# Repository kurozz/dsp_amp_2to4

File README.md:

DSP Amplifier - 2 inputs 4 outputs
Amplifier with DSP based on TPA3116D2 and ADAU1701 with 4 outputs and stereo input.

DSP programming can be done with SigmaStudio and needs an appropriate programmer.
How to program: https://daumemo.com/how-to-program-an-analog-devices-dsp/

Hackaday.io: https://hackaday.io/project/182993-dsp-amplifier-2-inputs-4-outputs
Project at PCBWAY (I get some credits if you buy the PCB from this link): https://www.pcbway.com/project/shareproject/DSP_Amplifier___2_inputs_4_outputs.html

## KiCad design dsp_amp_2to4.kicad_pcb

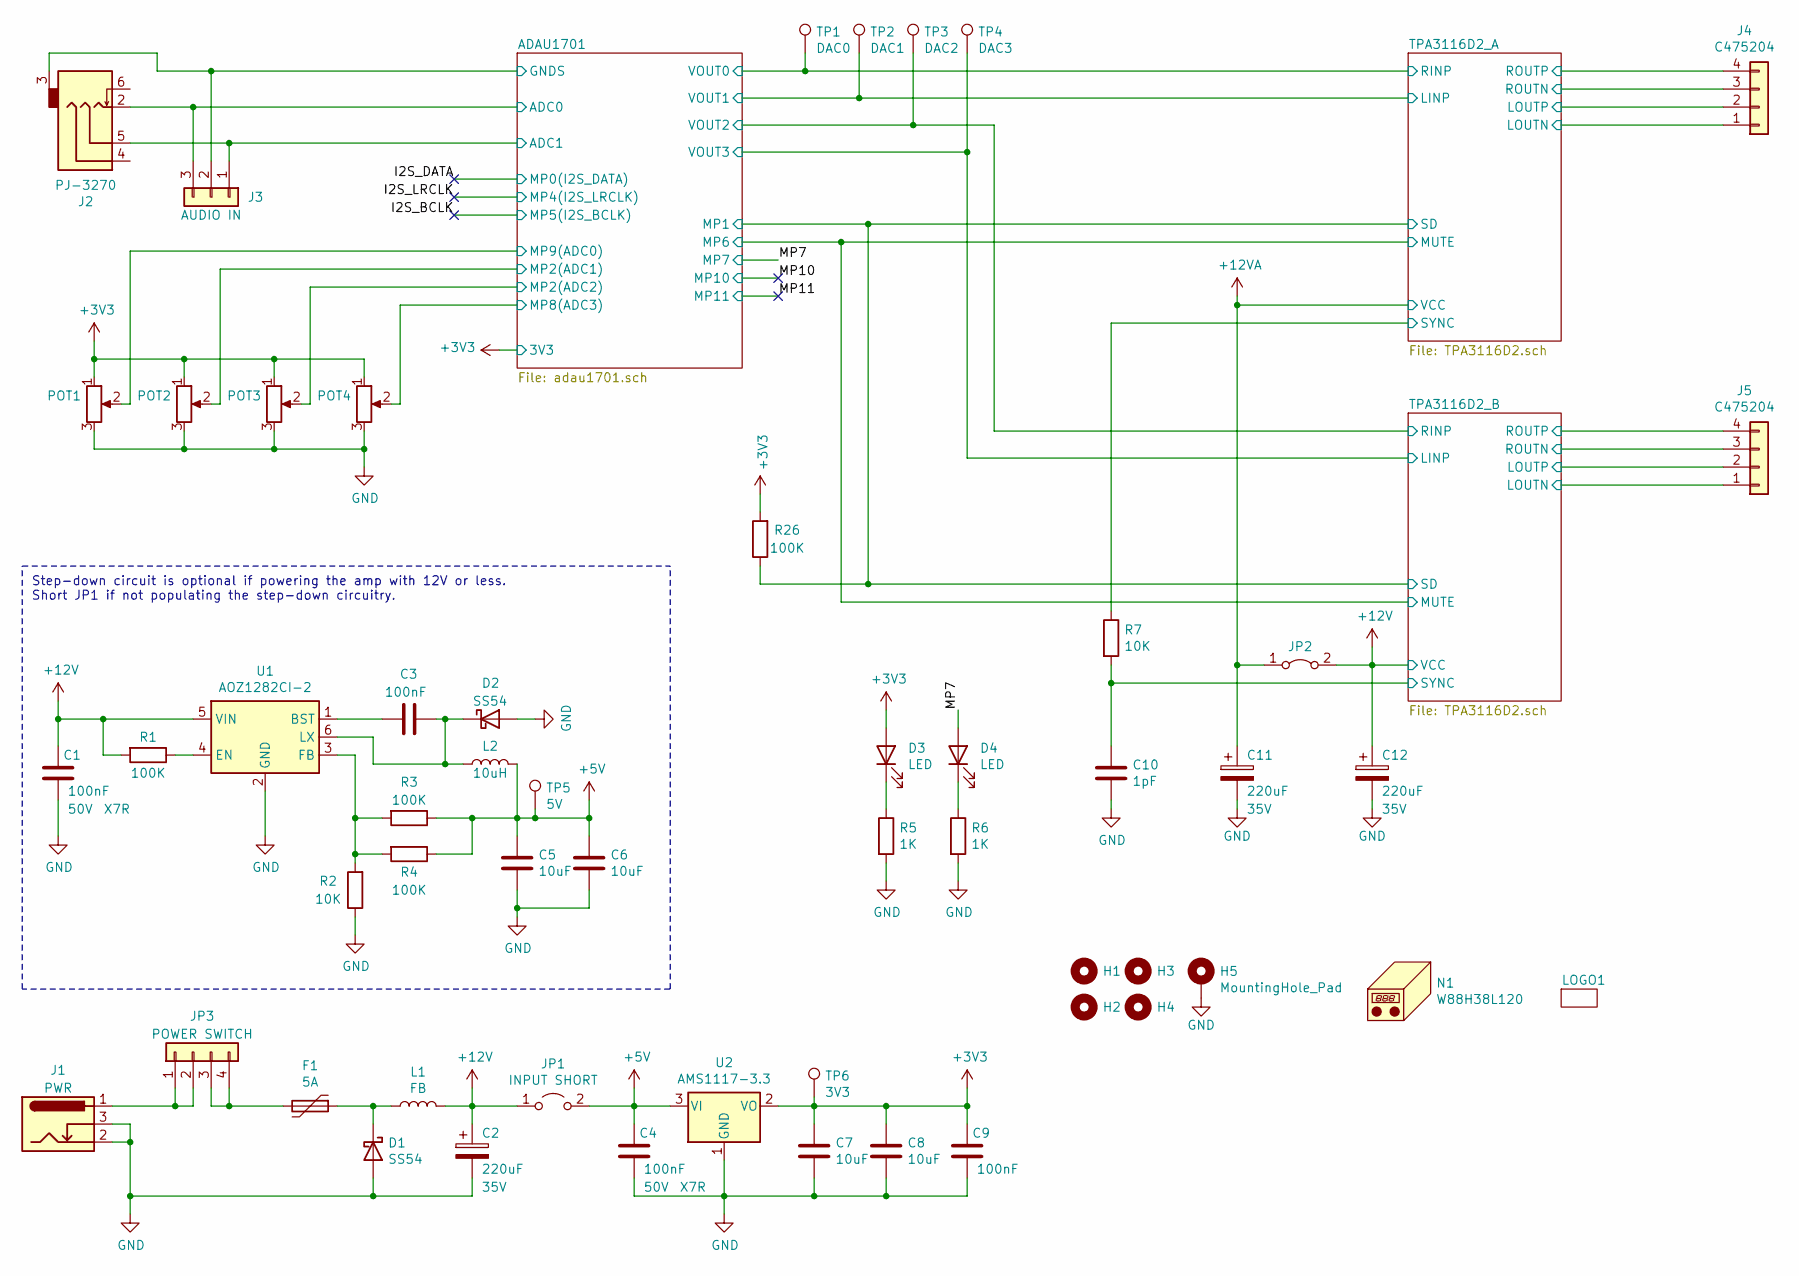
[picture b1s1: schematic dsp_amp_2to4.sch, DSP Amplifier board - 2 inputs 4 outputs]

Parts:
C1, C3, C4, C9: 100nF; C_0603_1608Metric; Rating X7R; Voltage 50V; LCSC Part Number C14663
C2, C11, C12: 220uF; CP_Radial_D8.0mm_P3.50mm; Voltage 35V; LCSC Part Number C433284
C5, C6, C7, C8: 10uF; C_0603_1608Metric; LCSC Part Number C85713
C10: 1pF; C_0603_1608Metric
D1, D2: SS54; D_SMA; LCSC Part Number C908681
D3, D4: LED; LED_D3.0mm; LCSC Part Number C710207
F1: 5A; Fuse_1206_3216Metric; LCSC Part Number C99541
H1, H2, H3, H4: MountingHole; MountingHole_3.2mm_M3
H5: MountingHole_Pad; MountingHole_3.2mm_M3_Pad_Via
J1: PWR; C381116; LCSC Part Number C381116
J2: PJ-3270; LCSC Part Number C381134
J3: JST XH-B3B; JST_XH_B3B-XH-A_1x03_P2.50mm_Vertical; LCSC Part Number C2316
J4, J5: C475204; LCSC Part Number C475204
JP1: INPUT SHORT; SolderJumper-2_P1.3mm_Open_TrianglePad1.0x1.5mm
JP2: Jumper Wire; R_Axial_DIN0204_L3.6mm_D1.6mm_P7.62mm_Horizontal
JP3: POWER SWITCH; JST_XH_B4B-XH-A_1x04_P2.50mm_Vertical
L1: FB; L_0805_2012Metric; LCSC Part Number C304323
L2: 10uH; L_6.3x6.3_H3; LCSC Part Number C207842
LOGO1: logo; shamiko
N1: W88H38L120; Aluminum_W88H38L120
POT1, POT2, POT3, POT4: JST XH-B3B; JST_XH_B3B-XH-A_1x03_P2.50mm_Vertical; LCSC Part Number C2316
R1, R3, R4, R26: 100K; R_0603_1608Metric; LCSC Part Number C14675
R2, R7: 10K; R_0603_1608Metric; LCSC Part Number C98220
R5, R6: 1K; R_0603_1608Metric; LCSC Part Number C22548
TP1: DAC0; TestPoint_THTPad_D1.0mm_Drill0.5mm
TP2: DAC1; TestPoint_THTPad_D1.0mm_Drill0.5mm
TP3: DAC2; TestPoint_THTPad_D1.0mm_Drill0.5mm
TP4: DAC3; TestPoint_THTPad_D1.0mm_Drill0.5mm
TP5: 5V; TestPoint_THTPad_D1.0mm_Drill0.5mm
TP6: 3V3; TestPoint_THTPad_D1.0mm_Drill0.5mm
U1: AOZ1282CI-2; SOT-23-6; LCSC Part Number C176766
U2: AMS1117-3.3; SOT-223-3_TabPin2; LCSC Part Number C347222

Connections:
+3V3: C7.1, C8.1, C9.1, D3.2 (A), POT1.1, POT2.1, POT3.1, POT4.1, R26.2, TP6.1, U2.2 (VO); also elsewhere on the board
+5V: C4.1, C5.1, C6.1, JP1.2 (B), L2.2, R3.1, R4.1, TP5.1, U2.3 (VI)
+12V: C1.1, C2.1, C12.1, JP1.1 (A), JP2.2 (B), L1.2, R1.2, U1.5 (VIN); also elsewhere on the board
+12VA: C11.1, JP2.1 (A); also elsewhere on the board
/ADAU1701/ADC0: J2.2, J3.3; also elsewhere on the board
/ADAU1701/ADC1: J2.5, J3.1; also elsewhere on the board
/ADAU1701/GNDS: J2.3, J3.2; also elsewhere on the board
/ADAU1701/MP1: R26.1; also elsewhere on the board
/ADAU1701/MP2(ADC1): POT2.2; also elsewhere on the board
/ADAU1701/MP2(ADC2): POT3.2; also elsewhere on the board
/ADAU1701/MP8(ADC3): POT4.2; also elsewhere on the board
/ADAU1701/MP9(ADC0): POT1.2; also elsewhere on the board
/MP7: D4.2 (A); also elsewhere on the board
/TPA3116D2_A/LINP: TP2.1; also elsewhere on the board
/TPA3116D2_A/LOUTN: J4.1; also elsewhere on the board
/TPA3116D2_A/LOUTP: J4.2; also elsewhere on the board
/TPA3116D2_A/RINP: TP1.1; also elsewhere on the board
/TPA3116D2_A/ROUTN: J4.3; also elsewhere on the board
/TPA3116D2_A/ROUTP: J4.4; also elsewhere on the board
/TPA3116D2_A/SYNC: R7.1; also elsewhere on the board
/TPA3116D2_B/LINP: TP4.1; also elsewhere on the board
/TPA3116D2_B/LOUTN: J5.1; also elsewhere on the board
/TPA3116D2_B/LOUTP: J5.2; also elsewhere on the board
/TPA3116D2_B/RINP: TP3.1; also elsewhere on the board
/TPA3116D2_B/ROUTN: J5.3; also elsewhere on the board
/TPA3116D2_B/ROUTP: J5.4; also elsewhere on the board
/TPA3116D2_B/SYNC: C10.1, R7.2; also elsewhere on the board
GND: C1.2, C2.2, C4.2, C5.2, C6.2, C7.2, C8.2, C9.2, C10.2, C11.2, C12.2, D1.2 (A), D2.2 (A), H5.1, J1.2, J1.3, POT1.3, POT2.3, POT3.3, POT4.3, R2.1, R5.2, R6.2, U1.2 (GND), U2.1 (GND); also elsewhere on the board
unnamed: C3.1, U1.1 (BST)
unnamed: C3.2, D2.1 (K), L2.1, U1.6 (LX)
unnamed: D1.1 (K), F1.1, L1.1
unnamed: D3.1 (K), R5.1
unnamed: D4.1 (K), R6.1
unnamed: F1.2, JP3.3, JP3.4
unnamed: J1.1, JP3.1, JP3.2
unnamed: R1.1, U1.4 (EN)
unnamed: R2.2, R3.2, R4.2, U1.3 (FB)

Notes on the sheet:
Step-down circuit is optional if powering the amp with 12V or less. Short JP1 if not populating the step-down circuitry.

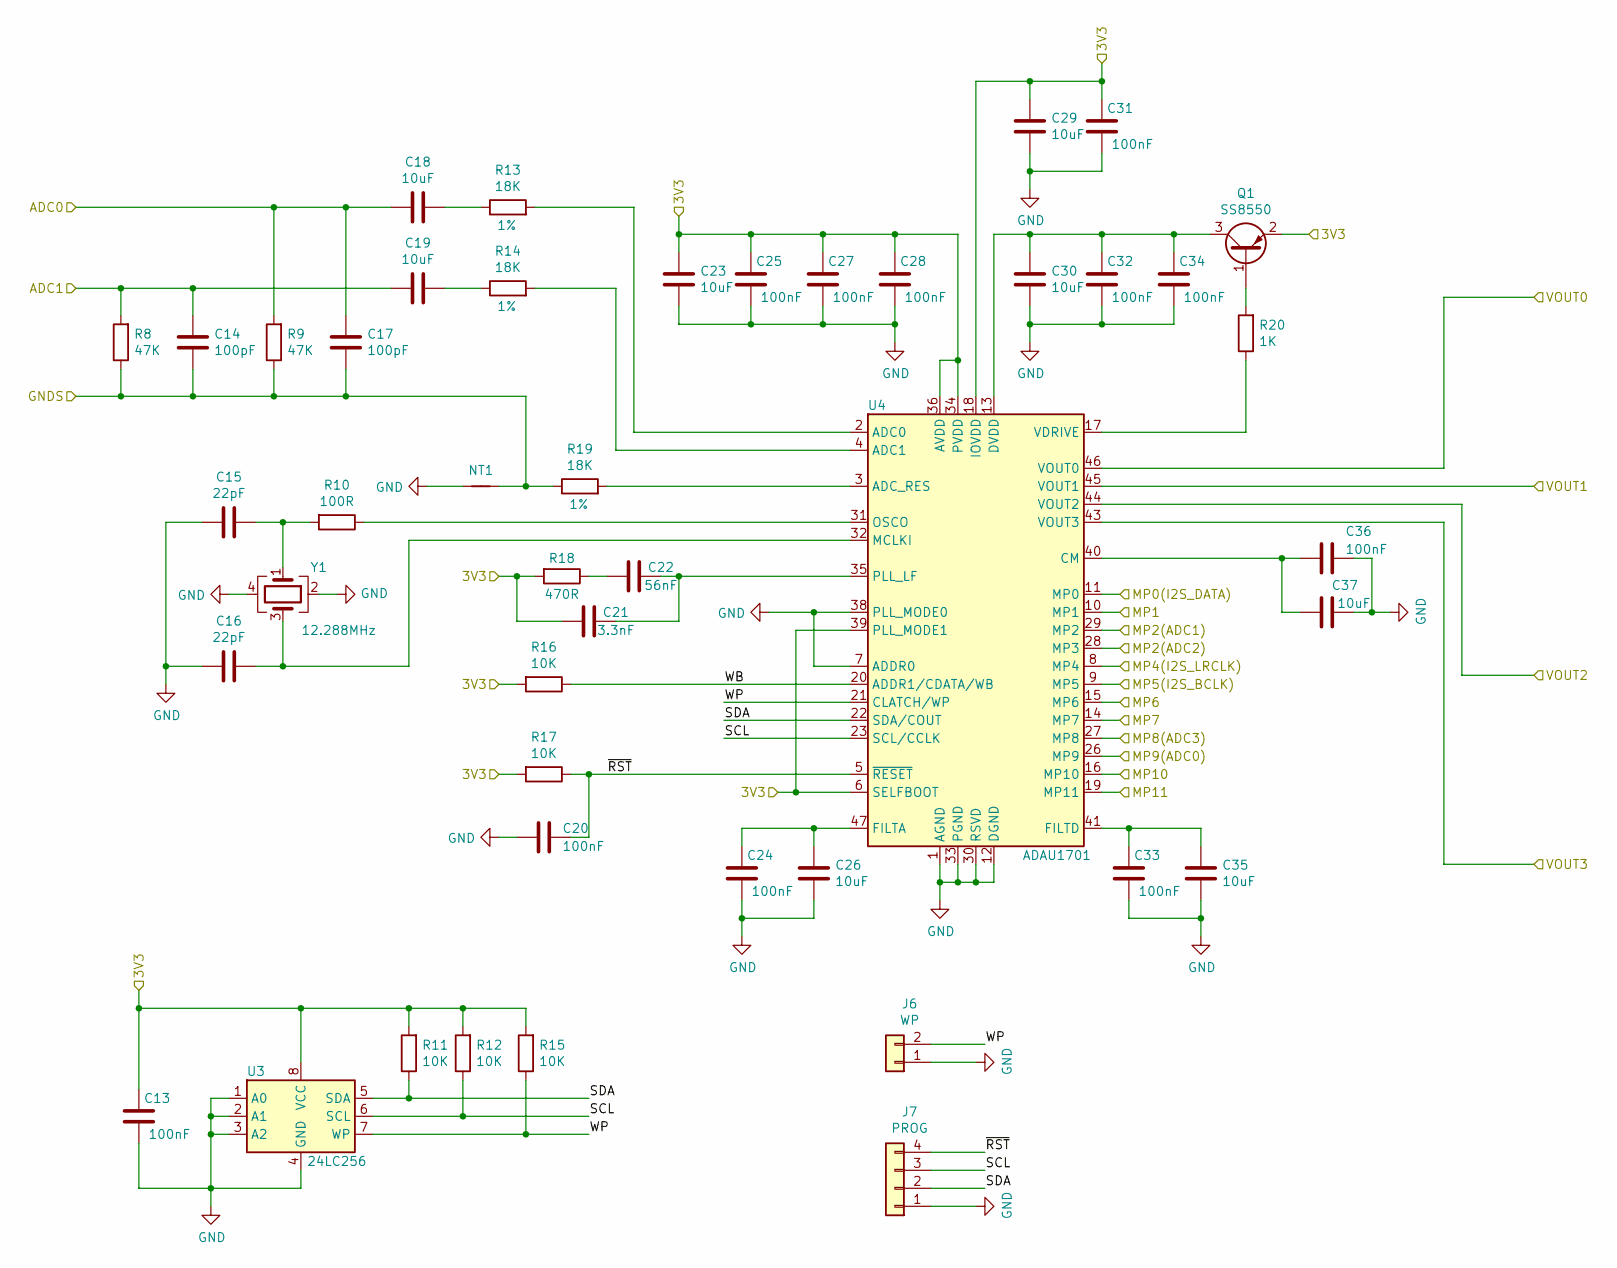
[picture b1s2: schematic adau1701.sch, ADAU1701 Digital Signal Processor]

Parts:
C13, C20, C24, C25, C27, C28, C31, C32, C33, C34, C36: 100nF; C_0603_1608Metric; Rating X7R; Voltage 50V; LCSC Part Number C14663
C14, C17: 100pF; C_0603_1608Metric; LCSC Part Number C14665
C15, C16: 22pF; C_0603_1608Metric; LCSC Part Number C105620
C18, C19, C23, C26, C29, C30, C35, C37: 10uF; C_0603_1608Metric; LCSC Part Number C85713
C21: 3.3nF; C_0603_1608Metric; LCSC Part Number C107088
C22: 56nF; C_0603_1608Metric; LCSC Part Number C282072
J6: WP; PinHeader_1x02_P2.54mm_Vertical
J7: PROG; PinHeader_1x04_P2.54mm_Vertical
NT1: Net-Tie_2; NetTie-2_SMD_Pad0.5mm
Q1: SS8550; SOT-23; LCSC Part Number C545534
R8, R9: 47K; R_0603_1608Metric; LCSC Part Number C105579
R10: 100R; R_0603_1608Metric; LCSC Part Number C105588
R11, R12, R15, R16, R17: 10K; R_0603_1608Metric; LCSC Part Number C98220
R13, R14, R19: 18K; R_0603_1608Metric; Tolerance 1%; LCSC Part Number C114610
R18: 470R; R_0603_1608Metric; LCSC Part Number C114669
R20: 1K; R_0603_1608Metric; LCSC Part Number C22548
U3: 24LC256; SOIC-8_3.9x4.9mm_P1.27mm; LCSC Part Number C5458
U4: ADAU1701; LQFP-48_7x7mm_P0.5mm; LCSC Part Number C389590
Y1: 12.288MHz; Crystal_SMD_SeikoEpson_FA238-4Pin_3.2x2.5mm; LCSC Part Number C389826

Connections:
+3V3: C13.1, C21.2, C23.1, C25.1, C27.1, C28.1, C29.1, C31.1, Q1.2 (E), R11.2, R12.2, R15.2, R16.2, R17.2, R18.2, U3.8 (VCC), U4.6 (SELFBOOT), U4.18 (IOVDD), U4.34 (PVDD), U4.36 (AVDD), U4.39 (PLL_MODE1), U4.48 (AVDD); also elsewhere on the board
/ADAU1701/ADC0: C17.2, C18.1, R9.2; also elsewhere on the board
/ADAU1701/ADC1: C14.2, C19.1, R8.2; also elsewhere on the board
/ADAU1701/GNDS: C14.1, C17.1, NT1.2, R8.1, R9.1, R19.1; also elsewhere on the board
/ADAU1701/MP1: U4.10 (MP1); also elsewhere on the board
/ADAU1701/MP2(ADC1): U4.29 (MP2); also elsewhere on the board
/ADAU1701/MP2(ADC2): U4.28 (MP3); also elsewhere on the board
/ADAU1701/MP6: U4.15 (MP6); also elsewhere on the board
/ADAU1701/MP8(ADC3): U4.27 (MP8); also elsewhere on the board
/ADAU1701/MP9(ADC0): U4.26 (MP9); also elsewhere on the board
/ADAU1701/SCL: J7.3, R12.1, U3.6 (SCL), U4.23 (SCL/CCLK)
/ADAU1701/SDA: J7.2, R11.1, U3.5 (SDA), U4.22 (SDA/COUT)
/ADAU1701/WB: R16.1, U4.20 (ADDR1/CDATA/WB)
/ADAU1701/WP: J6.2, R15.1, U3.7 (WP), U4.21 (CLATCH/WP)
/ADAU1701/~RST: C20.1, J7.4, R17.1, U4.5 (~RESET)
/I2S_BCLK: U4.9 (MP5)
/I2S_DATA: U4.11 (MP0)
/I2S_LRCLK: U4.8 (MP4)
/MP7: U4.14 (MP7); also elsewhere on the board
/MP10: U4.16 (MP10)
/MP11: U4.19 (MP11)
/TPA3116D2_A/LINP: U4.45 (VOUT1); also elsewhere on the board
/TPA3116D2_A/RINP: U4.46 (VOUT0); also elsewhere on the board
/TPA3116D2_B/LINP: U4.43 (VOUT3); also elsewhere on the board
/TPA3116D2_B/RINP: U4.44 (VOUT2); also elsewhere on the board
GND: C13.2, C15.1, C16.1, C20.2, C23.2, C24.2, C25.2, C26.2, C27.2, C28.2, C29.2, C30.2, C31.2, C32.2, C33.2, C34.2, C35.2, C36.1, C37.1, J6.1, J7.1, NT1.1, U3.1 (A0), U3.2 (A1), U3.3 (A2), U3.4 (GND), U4.1 (AGND), U4.7 (ADDR0), U4.12 (DGND), U4.25 (DGND), U4.30 (RSVD), U4.33 (PGND), U4.37 (AGND), U4.38 (PLL_MODE0), U4.42 (AGND), Y1.2, Y1.4; also elsewhere on the board
unnamed: C15.2, R10.2, Y1.1
unnamed: C16.2, U4.32 (MCLKI), Y1.3
unnamed: C18.2, R13.1
unnamed: C19.2, R14.1
unnamed: C21.1, C22.1, U4.35 (PLL_LF)
unnamed: C22.2, R18.1
unnamed: C24.1, C26.1, U4.47 (FILTA)
unnamed: C30.1, C32.1, C34.1, Q1.3 (C), U4.13 (DVDD), U4.24 (DVDD)
unnamed: C33.1, C35.1, U4.41 (FILTD)
unnamed: C36.2, C37.2, U4.40 (CM)
unnamed: Q1.1 (B), R20.2
unnamed: R10.1, U4.31 (OSCO)
unnamed: R13.2, U4.2 (ADC0)
unnamed: R14.2, U4.4 (ADC1)
unnamed: R19.2, U4.3 (ADC_RES)
unnamed: R20.1, U4.17 (VDRIVE)

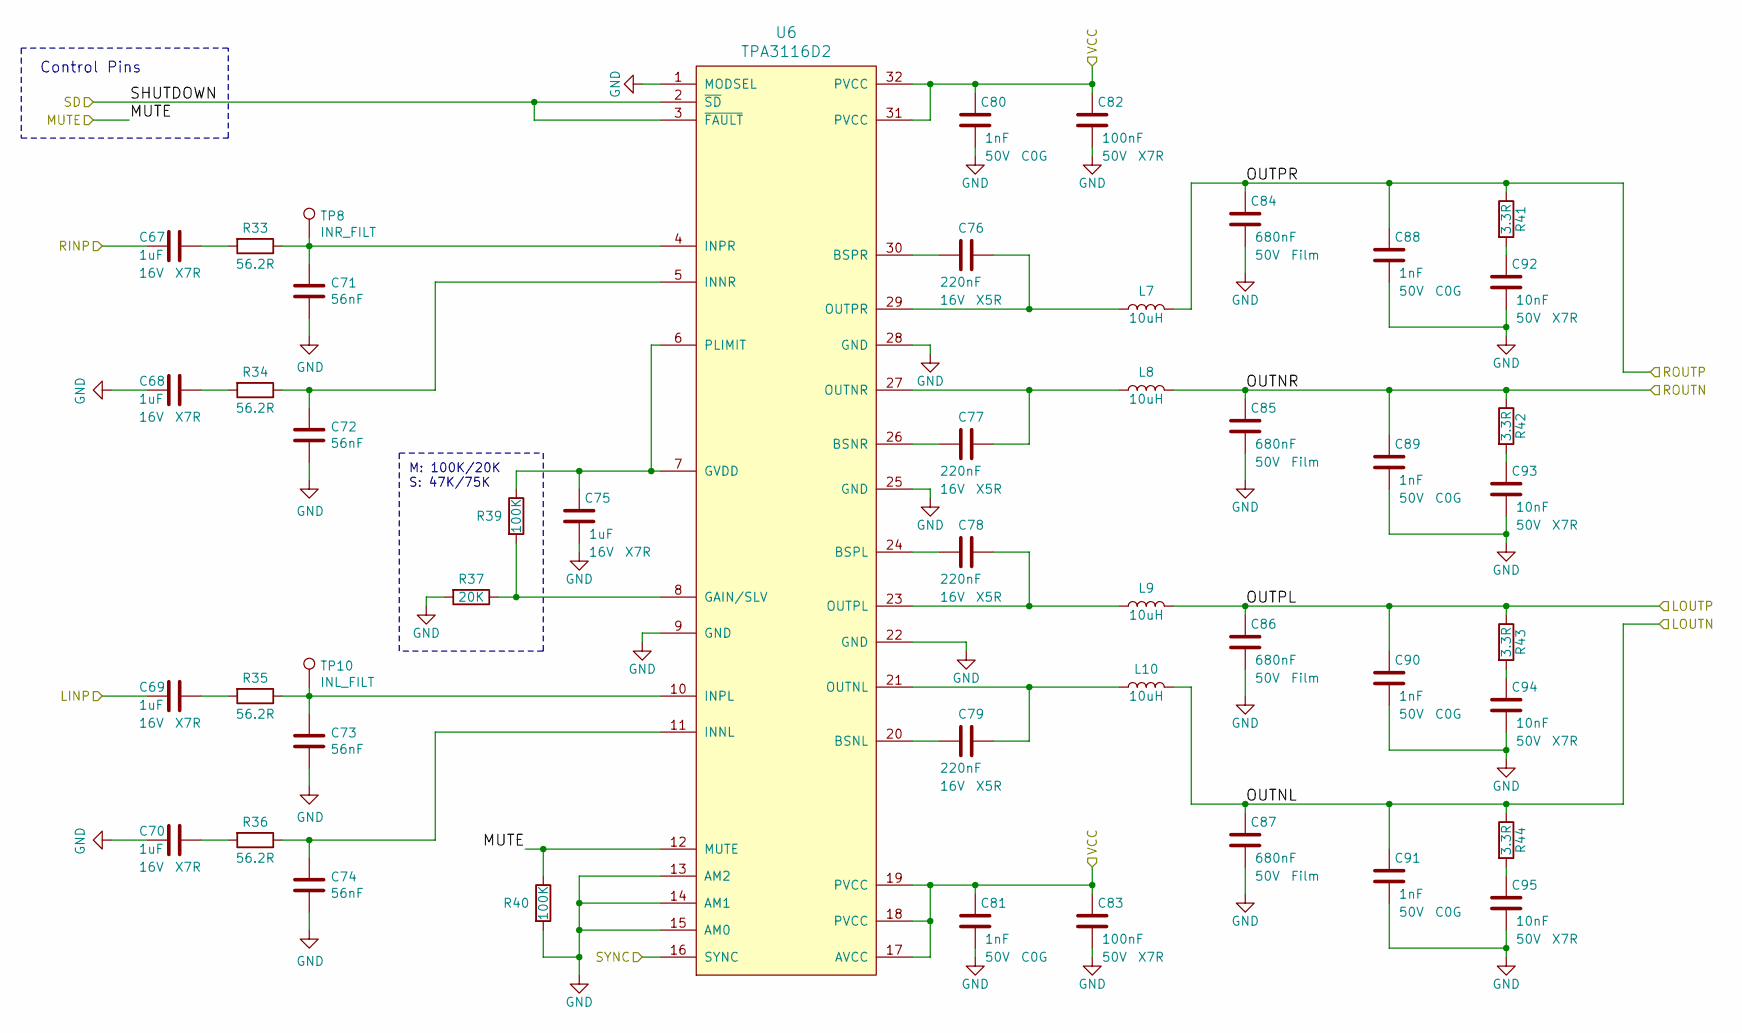
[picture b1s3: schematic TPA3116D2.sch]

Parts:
C38, C39, C40, C41, C46: 1uF; C_0603_1608Metric; Rating X7R; Voltage 16V; LCSC Part Number C59782
C42, C43, C44, C45: 56nF; C_0603_1608Metric; LCSC Part Number C282072
C47, C48, C49, C50: 220nF; C_0603_1608Metric; Rating X5R; Voltage 16V; LCSC Part Number C21120
C51, C52, C59, C60, C61, C62: 1nF; C_0603_1608Metric; Rating C0G; Voltage 50V; LCSC Part Number C163508
C53, C54: 100nF; C_0603_1608Metric; Rating X7R; Voltage 50V; LCSC Part Number C14663
C55, C56, C57, C58: 680nF; C_Rect_L7.0mm_W4.5mm_P5.00mm; Rating Film; Voltage 50V; LCSC Part Number C280298
C63, C64, C65, C66: 10nF; C_0603_1608Metric; Rating X7R; Voltage 50V; LCSC Part Number C107059
L3, L4, L5, L6: 10uH; L_6.3x6.3_H3; LCSC Part Number C207842
R21, R22, R23, R24: 56.2R; R_0603_1608Metric; LCSC Part Number C137698
R25: 20K; R_0603_1608Metric; LCSC Part Number C105575
R27, R28: 100K; R_0603_1608Metric; LCSC Part Number C14675
R29, R30, R31, R32: 3.3R; R_0603_1608Metric; LCSC Part Number C137725
TP7: INR_FILT; TestPoint_Pad_D1.0mm
TP9: INL_FILT; TestPoint_Pad_D1.0mm
U5: TPA3116D2; HTSSOP-32-1EP_6.1x11mm_P0.65mm_EP5.2x11mm_Mask4.11x4.36mm_T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; LCSC Part Number C50144

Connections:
+12VA: C51.1, C52.1, C53.1, C54.1, U5.17 (AVCC), U5.18 (PVCC), U5.19 (PVCC), U5.31 (PVCC), U5.32 (PVCC); also elsewhere on the board
/ADAU1701/MP1: U5.2 (~SD), U5.3 (~FAULT); also elsewhere on the board
/ADAU1701/MP6: R28.1, U5.12 (MUTE); also elsewhere on the board
/TPA3116D2_A/LINP: C40.2; also elsewhere on the board
/TPA3116D2_A/LOUTN: C58.1, C62.1, L6.2, R32.1; also elsewhere on the board
/TPA3116D2_A/LOUTP: C57.1, C61.1, L5.2, R31.1; also elsewhere on the board
/TPA3116D2_A/RINP: C38.2; also elsewhere on the board
/TPA3116D2_A/ROUTN: C56.1, C60.1, L4.2, R30.1; also elsewhere on the board
/TPA3116D2_A/ROUTP: C55.1, C59.1, L3.2, R29.1; also elsewhere on the board
/TPA3116D2_A/SYNC: U5.16 (SYNC); also elsewhere on the board
GND: C39.2, C41.2, C42.2, C43.2, C44.2, C45.2, C46.2, C51.2, C52.2, C53.2, C54.2, C55.2, C56.2, C57.2, C58.2, C59.2, C60.2, C61.2, C62.2, C63.2, C64.2, C65.2, C66.2, R25.2, R28.2, U5.1 (MODSEL), U5.9 (GND), U5.13 (AM2), U5.14 (AM1), U5.15 (AM0), U5.22 (GND), U5.25 (GND), U5.28 (GND), U5.33 (GND); also elsewhere on the board
unnamed: C38.1, R21.2
unnamed: C39.1, R22.2
unnamed: C40.1, R23.2
unnamed: C41.1, R24.2
unnamed: C42.1, R21.1, TP7.1, U5.4 (INPR)
unnamed: C43.1, R22.1, U5.5 (INNR)
unnamed: C44.1, R23.1, TP9.1, U5.10 (INPL)
unnamed: C45.1, R24.1, U5.11 (INNL)
unnamed: C46.1, R27.1, U5.6 (PLIMIT), U5.7 (GVDD)
unnamed: C47.1, L3.1, U5.29 (OUTPR)
unnamed: C47.2, U5.30 (BSPR)
unnamed: C48.1, L4.1, U5.27 (OUTNR)
unnamed: C48.2, U5.26 (BSNR)
unnamed: C49.1, L5.1, U5.23 (OUTPL)
unnamed: C49.2, U5.24 (BSPL)
unnamed: C50.1, L6.1, U5.21 (OUTNL)
unnamed: C50.2, U5.20 (BSNL)
unnamed: C63.1, R29.2
unnamed: C64.1, R30.2
unnamed: C65.1, R31.2
unnamed: C66.1, R32.2
unnamed: R25.1, R27.2, U5.8 (GAIN/SLV)

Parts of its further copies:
C67, C68, C69, C70, C75: 1uF; C_0603_1608Metric; Rating X7R; Voltage 16V; LCSC Part Number C59782
C71, C72, C73, C74: 56nF; C_0603_1608Metric; LCSC Part Number C282072
C76, C77, C78, C79: 220nF; C_0603_1608Metric; Rating X5R; Voltage 16V; LCSC Part Number C21120
C80, C81, C88, C89, C90, C91: 1nF; C_0603_1608Metric; Rating C0G; Voltage 50V; LCSC Part Number C163508
C82, C83: 100nF; C_0603_1608Metric; Rating X7R; Voltage 50V; LCSC Part Number C14663
C84, C85, C86, C87: 680nF; C_Rect_L7.0mm_W4.5mm_P5.00mm; Rating Film; Voltage 50V; LCSC Part Number C280298
C92, C93, C94, C95: 10nF; C_0603_1608Metric; Rating X7R; Voltage 50V; LCSC Part Number C107059
L7, L8, L9, L10: 10uH; L_6.3x6.3_H3; LCSC Part Number C207842
R33, R34, R35, R36: 56.2R; R_0603_1608Metric; LCSC Part Number C137698
R37: 20K; R_0603_1608Metric; LCSC Part Number C105575
R39, R40: 100K; R_0603_1608Metric; LCSC Part Number C14675
R41, R42, R43, R44: 3.3R; R_0603_1608Metric; LCSC Part Number C137725
TP8: INR_FILT; TestPoint_Pad_D1.0mm
TP10: INL_FILT; TestPoint_Pad_D1.0mm
U6: TPA3116D2; HTSSOP-32-1EP_6.1x11mm_P0.65mm_EP5.2x11mm_Mask4.11x4.36mm_T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; LCSC Part Number C50144

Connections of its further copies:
+12V: C80.1, C81.1, C82.1, C83.1, U6.17 (AVCC), U6.18 (PVCC), U6.19 (PVCC), U6.31 (PVCC), U6.32 (PVCC); also elsewhere on the board
/ADAU1701/MP1: U6.2 (~SD), U6.3 (~FAULT); also elsewhere on the board
/ADAU1701/MP6: R40.1, U6.12 (MUTE); also elsewhere on the board
/TPA3116D2_B/LINP: C69.2; also elsewhere on the board
/TPA3116D2_B/LOUTN: C87.1, C91.1, L10.2, R44.1; also elsewhere on the board
/TPA3116D2_B/LOUTP: C86.1, C90.1, L9.2, R43.1; also elsewhere on the board
/TPA3116D2_B/RINP: C67.2; also elsewhere on the board
/TPA3116D2_B/ROUTN: C85.1, C89.1, L8.2, R42.1; also elsewhere on the board
/TPA3116D2_B/ROUTP: C84.1, C88.1, L7.2, R41.1; also elsewhere on the board
/TPA3116D2_B/SYNC: U6.16 (SYNC); also elsewhere on the board
GND: C68.2, C70.2, C71.2, C72.2, C73.2, C74.2, C75.2, C80.2, C81.2, C82.2, C83.2, C84.2, C85.2, C86.2, C87.2, C88.2, C89.2, C90.2, C91.2, C92.2, C93.2, C94.2, C95.2, R37.2, R40.2, U6.1 (MODSEL), U6.9 (GND), U6.13 (AM2), U6.14 (AM1), U6.15 (AM0), U6.22 (GND), U6.25 (GND), U6.28 (GND), U6.33 (GND); also elsewhere on the board
unnamed: C67.1, R33.2
unnamed: C68.1, R34.2
unnamed: C69.1, R35.2
unnamed: C70.1, R36.2
unnamed: C71.1, R33.1, TP8.1, U6.4 (INPR)
unnamed: C72.1, R34.1, U6.5 (INNR)
unnamed: C73.1, R35.1, TP10.1, U6.10 (INPL)
unnamed: C74.1, R36.1, U6.11 (INNL)
unnamed: C75.1, R39.1, U6.6 (PLIMIT), U6.7 (GVDD)
unnamed: C76.1, L7.1, U6.29 (OUTPR)
unnamed: C76.2, U6.30 (BSPR)
unnamed: C77.1, L8.1, U6.27 (OUTNR)
unnamed: C77.2, U6.26 (BSNR)
unnamed: C78.1, L9.1, U6.23 (OUTPL)
unnamed: C78.2, U6.24 (BSPL)
unnamed: C79.1, L10.1, U6.21 (OUTNL)
unnamed: C79.2, U6.20 (BSNL)
unnamed: C92.1, R41.2
unnamed: C93.1, R42.2
unnamed: C94.1, R43.2
unnamed: C95.1, R44.2
unnamed: R37.1, R39.2, U6.8 (GAIN/SLV)

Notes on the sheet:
Control Pins
M: 100K/20K S: 47K/75K

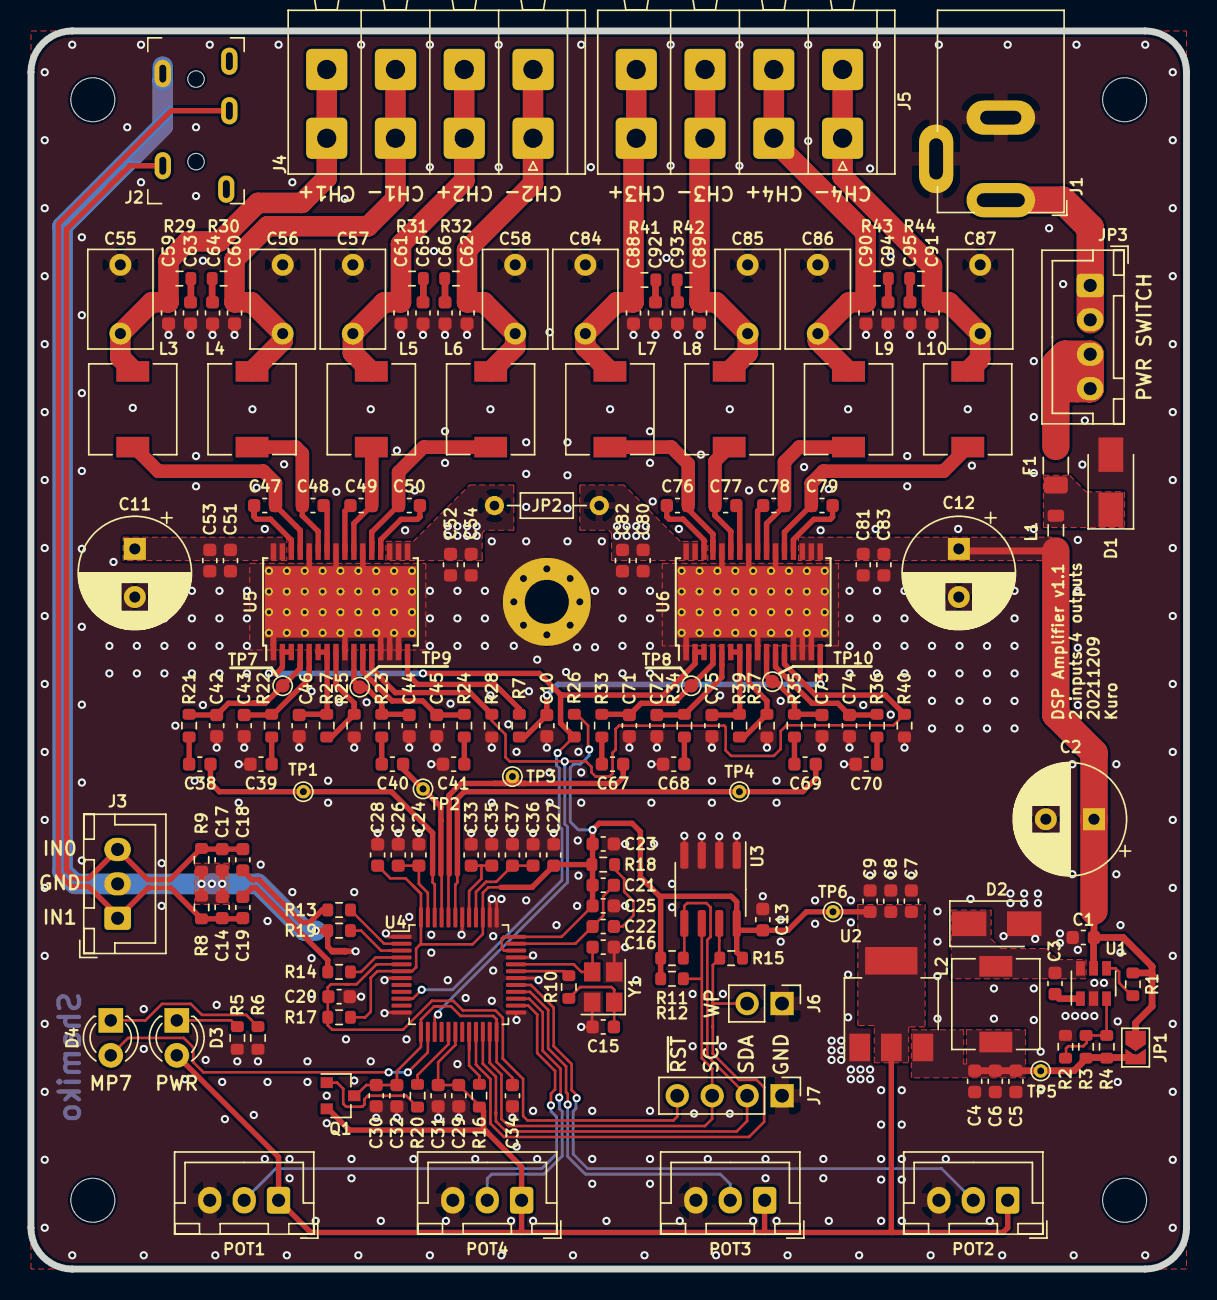
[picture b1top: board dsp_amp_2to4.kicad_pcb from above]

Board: 2 copper layers, 84.0 x 90.0 mm, 193 parts (1 on the bottom side), 103 nets.

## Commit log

2021-12-09 Create a
